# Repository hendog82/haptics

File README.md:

# haptics
haptic pants

https://www.hendog-blog.com/projects/Haptic_Pants

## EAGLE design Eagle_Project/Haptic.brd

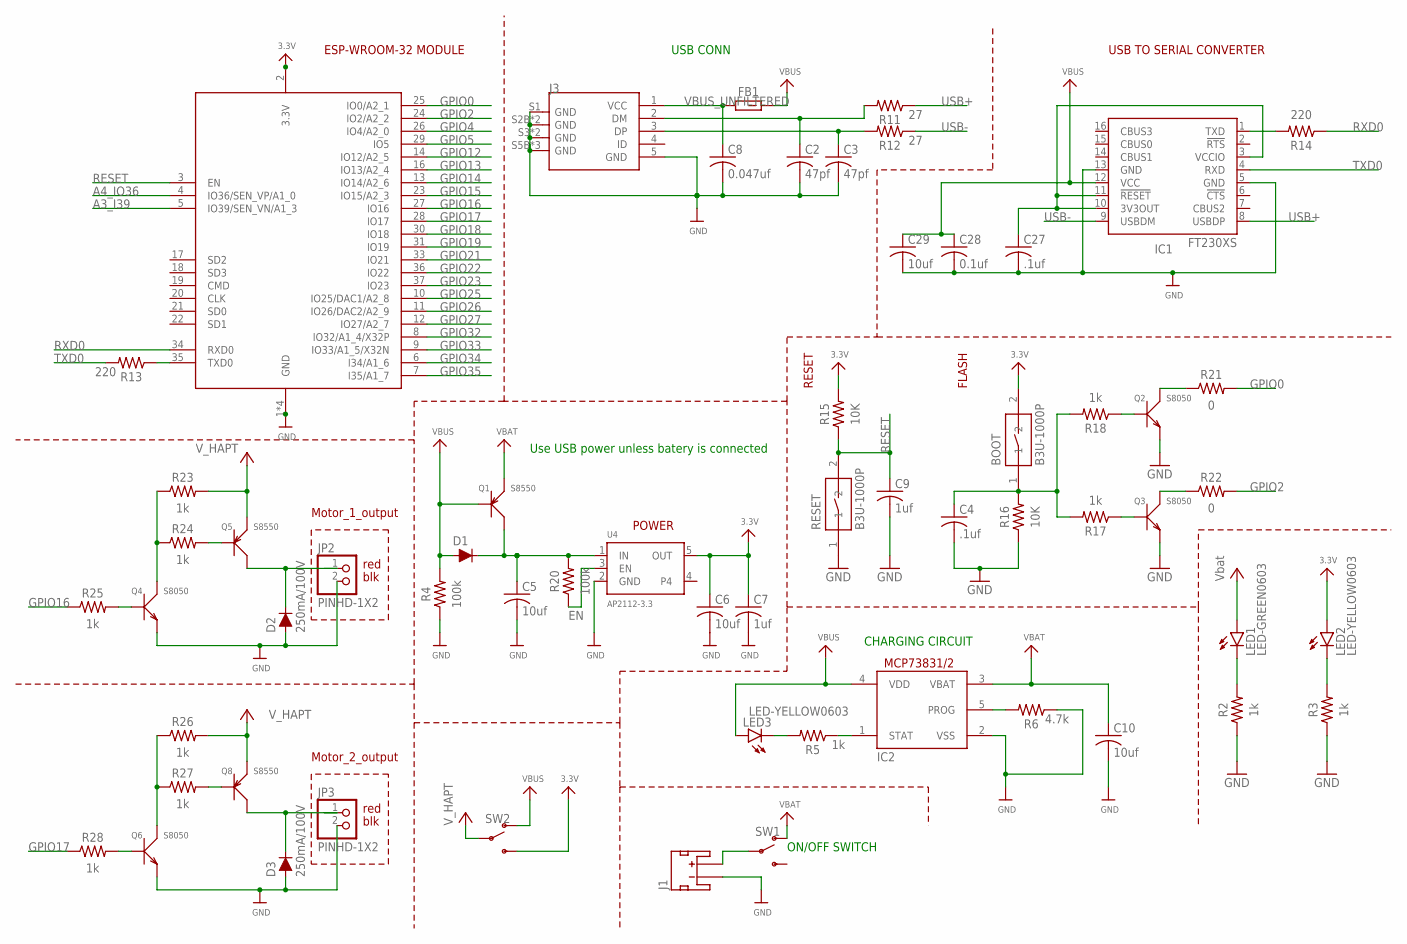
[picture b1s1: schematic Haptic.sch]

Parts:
BOOT: B3U-1000P
C2, C3: 47pf; CAPC1608X85
C4, C27: .1uf; CAPC1608X85
C5, C6, C10, C29: 10uf; CAPC1608X85
C7, C9: 1uf; CAPC1608X85
C8: 0.047uf; CAPC1608X85
C28: 0.1uf; CAPC1608X85
D1, D2, D3: 250mA/100V; SOD-323
FB1: BK1608TS601-T; BEADC1608X95N
IC1: FT230XS; SSOP16
IC2: MCP73831/OT; SOT23-5L
J1: JST_2MM_MALE; JST-2-SMD
J3: 10118193-0001LF; MICRO-USB5+6P-SMD-0.65-B
JP2, JP3: PINHD-1X2; 1X02
LED1: LED-GREEN0603; 0603-GREEN
LED2, LED3: LED-YELLOW0603; 0603-YELLOW
Q1, Q5, Q8: S8550; SOT-23
Q2, Q3, Q4, Q6: S8050; SOT-23
R2, R3, R5, R17, R18, R23, R24, R25, R26, R27, R28: 1k; RESC1608X60
R4, R20: 100k; RESC1608X60
R6: 4.7k; RESC1608X60
R11, R12: 27; RESC1608X60
R13, R14: 220; RESC1608X60
R15, R16: 10K; RESC1608X60
R21, R22: 0; RESC1608X60
RESET: B3U-1000P
SW1, SW2: SWITCH-SPDT-SMD-RIGHT-ANGLE; SWITCH_SPST_SMD_A
U4: AP2112-3.3; SOT23-5
X6: ESP32_WROOM32_SKINNY; WROOM32_SKINNY

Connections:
3.3V: BOOT.2, C6.1, C7.1, LED2.A, R15.2, SW2.3 (S), U4.5 (OUT), X6.2 (3.3V)
A3_I39: X6.5 (IO39/SEN_VN/A1_3)
A4_IO36: X6.4 (IO36/SEN_VP/A1_0)
EN: R20.1, U4.3 (EN)
GND: C2.2, C3.2, C4.2, C5.2, C6.2, C7.2, C8.2, C9.2, C10.2, C27.2, C28.2, C29.2, D2.A, D3.A, IC1.5 (GND), IC1.13 (GND), IC2.2 (VSS), J1.1 (-), J3.5 (GND), J3.S1 (GND), J3.S2B (GND), J3.S2T (GND), J3.S3 (GND), J3.S4 (GND), J3.S5B (GND), J3.S5T (GND), J3.S6 (GND), JP2.2, JP3.2, Q2.2 (E), Q3.2 (E), Q4.2 (E), Q6.2 (E), R2.1, R3.1, R4.1, R6.1, R16.1, RESET.1, U4.2 (GND), X6.1 (GND), X6.15 (GND), X6.38 (GND), X6.P$1 (GND)
GPIO0: R21.2, X6.25 (IO0/A2_1)
GPIO2: R22.2, X6.24 (IO2/A2_2)
GPIO4: X6.26 (IO4/A2_0)
GPIO5: X6.29 (IO5)
GPIO12: X6.14 (IO12/A2_5)
GPIO13: X6.16 (IO13/A2_4)
GPIO14: X6.13 (IO14/A2_6)
GPIO15: X6.23 (IO15/A2_3)
GPIO16: R25.1, X6.27 (IO16)
GPIO17: R28.1, X6.28 (IO17)
GPIO18: X6.30 (IO18)
GPIO19: X6.31 (IO19)
GPIO21: X6.33 (IO21)
GPIO22: X6.36 (IO22)
GPIO23: X6.37 (IO23)
GPIO25: X6.10 (IO25/DAC1/A2_8)
GPIO26: X6.11 (IO26/DAC2/A2_9)
GPIO27: X6.12 (IO27/A2_7)
GPIO32: X6.8 (IO32/A1_4/X32P)
GPIO33: X6.9 (IO33/A1_5/X32N)
GPIO34: X6.6 (I34/A1_6)
GPIO35: X6.7 (I35/A1_7)
unnamed: LED2.C, R3.2
unnamed: LED1.C, R2.2
unnamed: C2.1, J3.2 (DM), R11.2
unnamed: C3.1, J3.3 (DP), R12.2
unnamed: C27.1, IC1.3 (VCCIO), IC1.10 (3V3OUT), IC1.11 (!RESET)
unnamed: R13.1, X6.35 (TXD0)
unnamed: IC1.1 (TXD), R14.2
unnamed: BOOT.1, C4.1, R16.2, R17.2, R18.2
unnamed: Q2.1 (B), R18.1
unnamed: Q3.1 (B), R17.1
unnamed: Q3.3 (C), R22.1
unnamed: Q2.3 (C), R21.1
unnamed: Q4.1 (B), R25.2
unnamed: IC2.5 (PROG), R6.2
unnamed: IC2.1 (STAT), R5.1
unnamed: Q4.3 (C), R23.1, R24.1
unnamed: Q5.1 (B), R24.2
unnamed: Q6.1 (B), R28.2
unnamed: D2.C, JP2.1, Q5.3 (C)
unnamed: LED3.C, R5.2
unnamed: J1.2 (+), SW1.2
unnamed: Q6.3 (C), R26.1, R27.1
unnamed: Q8.1 (B), R27.2
unnamed: C5.1, D1.C, Q1.3 (C), R20.2, U4.1 (IN)
unnamed: D3.C, JP3.1, Q8.3 (C)
RESET: C9.1, R15.1, RESET.2, X6.3 (EN)
RXD0: R14.1, X6.34 (RXD0)
TXD0: IC1.4 (RXD), R13.2
USB+: IC1.8 (USBDP), R12.1
USB-: IC1.9 (USBDM), R11.1
VBAT: C10.1, IC2.3 (VBAT), Q1.2 (E), SW1.1 (O)
VBUS: C28.1, C29.1, D1.A, FB1.2, IC1.12 (VCC), IC2.4 (VDD), LED3.A, Q1.1 (B), R4.2, SW2.1 (O)
VBUS_UNFILTERED: C8.1, FB1.1, J3.1 (VCC)
VCC: LED1.A, Q5.2 (E), Q8.2 (E), R23.2, R26.2, SW2.2

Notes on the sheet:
POWER
RESET
USB TO SERIAL CONVERTER
ESP-WROOM-32 MODULE
FLASH
Motor_2_output
Motor_1_output
red
blk
Use USB power unless batery is connected
ON/OFF SWITCH
CHARGING CIRCUIT
USB CONN

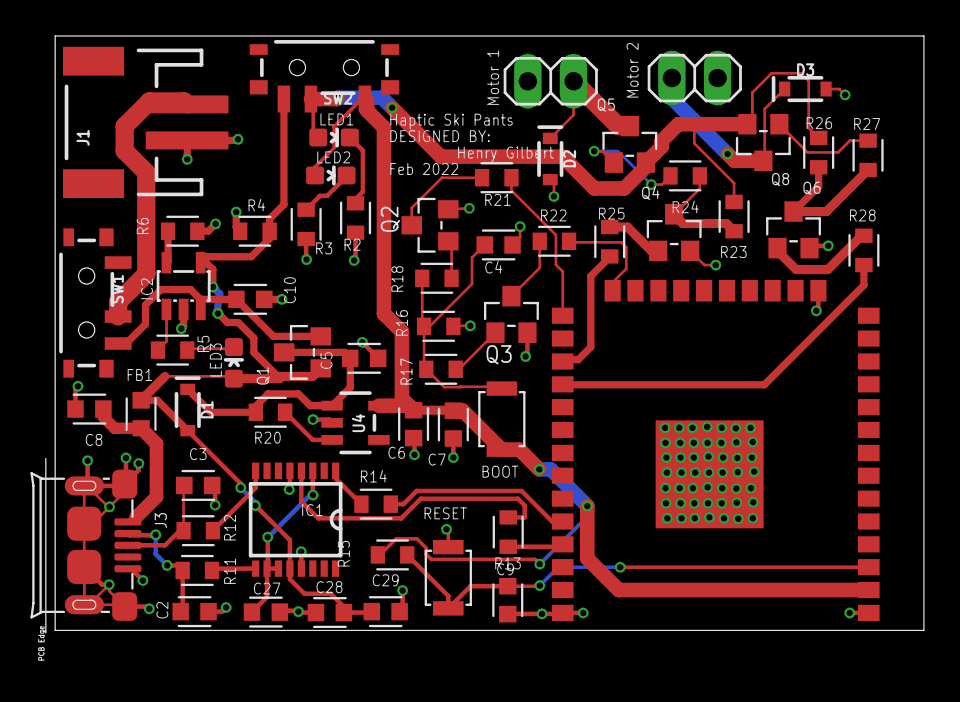
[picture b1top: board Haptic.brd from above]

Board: 2 copper layers, 48.8 x 33.1 mm, 60 parts (0 on the bottom side), 41 nets.

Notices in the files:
parts and their libraries:
microbuilder: This work is placed in the public domain, and may be freely used for commercial and non-commercial work with the following conditions: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
SparkFun-DiscreteSemi: Licensing: Creative Commons ShareAlike 4.0 International - https://creativecommons.org/licenses/by-sa/4.0
